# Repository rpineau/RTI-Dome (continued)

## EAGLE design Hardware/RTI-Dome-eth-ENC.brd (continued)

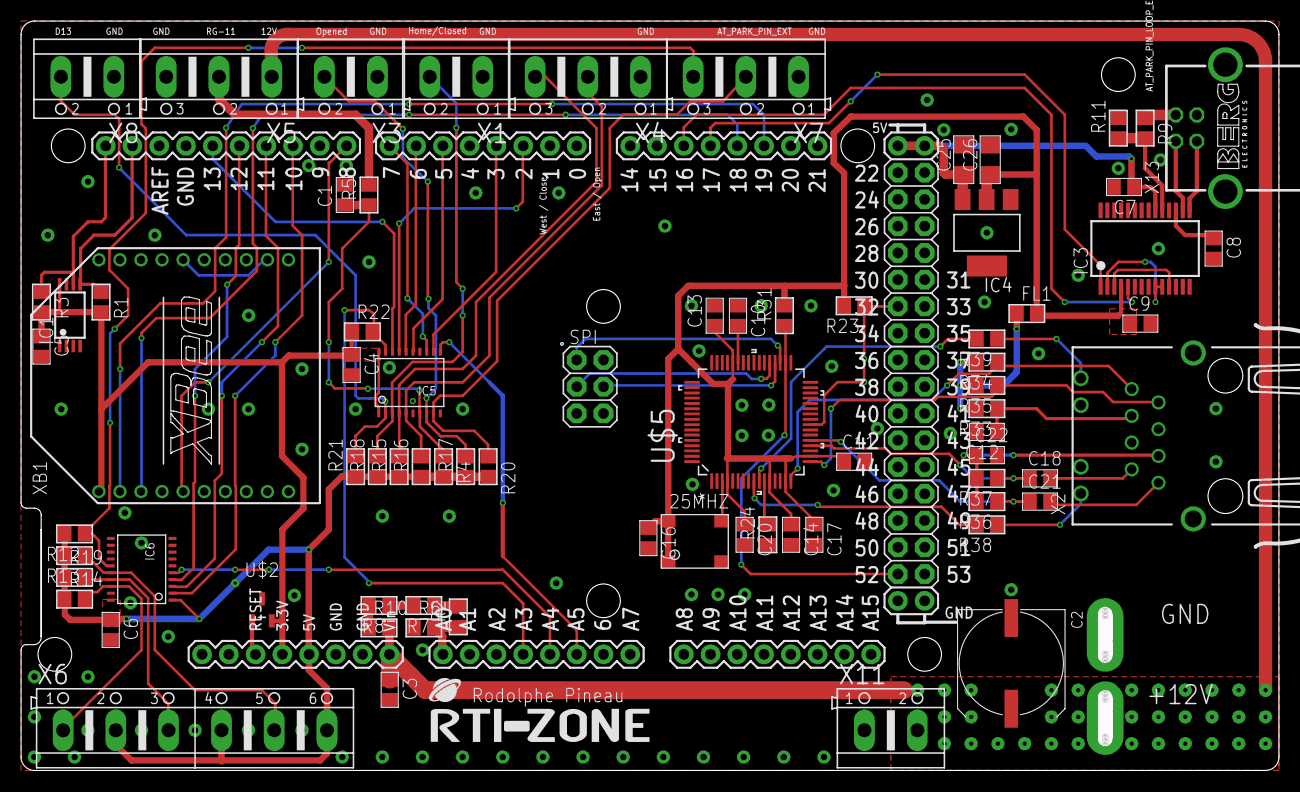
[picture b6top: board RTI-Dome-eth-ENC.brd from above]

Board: 2 copper layers, 119.4 x 71.1 mm, 77 parts (1 on the bottom side), 70 nets.

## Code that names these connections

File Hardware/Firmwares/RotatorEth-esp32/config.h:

//
// Firmware configuration
// Copyright © 2025 Rodolphe Pineau. All rights reserved.
//
#ifndef __R_CONFIG__
#define __R_CONFIG__
// #define DEBUG   // enable debug to serial port defined as DebugPort
// #define DEBUG_TO_COMPUTER // send all debug to usb serial instead of 3 pin serial debug.
// #define MOTION_LOG	// log all call to a motion function
#ifdef DEBUG
#pragma message "Debug messages enabled"
#ifndef DEBUG_TO_COMPUTER
#define DebugPort Serial1    //  Rx2,Tx2 =  Serial1
#endif
#define DBPrint(x) if(DebugPort) DebugPort.print(x)
#define DBPrintln(x) if(DebugPort) DebugPort.println(x)
#define DBPrintHex(x) if(DebugPort) DebugPort.print(x, HEX)
#else
#pragma message "Debug messages disabled"
#define DBPrint(x)
#define DBPrintln(x)
#define DBPrintHex(x)
#endif // DEBUG

#define VERSION "3.000"

#define USE_ALPACA
#define USE_OTA_UPDATE
// if uncommented, USE_WIFI will enable all code related to the shutter over WiFi.
// This is useful for people who only want to automate the rotation.
#define USE_WIFI

#define Computer Serial     // USB = Serial
#ifdef DEBUG
#ifdef DEBUG_TO_COMPUTER
#define DebugPort Serial
#endif
#endif
//
// ESP32 dev boards
//
// input
#define HOME_PIN            15  // Also used for Shutter open status
#define SPARE_OPENED_PIN 	33	// Digital Input, shutter open limit swith, not used on rotator board, spare input.
#define BUTTON_CCW          27 // Digital Input
#define BUTTON_CW           14 // Digital Input
#define CONDITION_SENSOR_PIN     25  // Digital Input from RG11 and other similar devices
#define SPARE1				34	 // no pull-up on this input pin
#define SPARE2				26
// ouput
#define STEPPER_ENABLE_PIN  13  // Digital Output
#define DIRECTION_PIN        2  // Digital Output
#define STEP_PIN            32  // Digital Output
// 100k to ground on GPIO 12, and 100k to 3.3V on GPIO 0
#define SPARE_OUT1			 0
#define SPARE_OUT2			12

#define MOVE_NEGATIVE       -1
#define MOVE_NONE            0
#define MOVE_POSITIVE        1

// #define M_ENABLE    HIGH
// #define M_DISABLE   LOW
#define M_ENABLE    LOW
#define M_DISABLE   HIGH

// A4988
//#define M_ENABLE    LOW
//#define M_DISABLE   HIGH

#define MAX_SPEED           8000
#define ACCELERATION        7000

#define DELAY_WIFI			10

/*
Micro-steps per rotation with a 200 step per rotation stepper and 15.3:1 gearbox
	NexDome 2m      : 440640
	Explora-Dome 8' : 479800
*/

#define STEPS_DEFAULT       440640

#define ETHERNET_CS     5
#define ETHERNET_INT	-1
#define ETHERNET_RESET  4
#define CMD_SERVER_PORT 2323

// network interfaces
#include <ETH.h>
#include <Network.h>
#define domeEthernet ETH

#define ETH_PHY_TYPE ETH_PHY_W5500
#define ETH_PHY_ADDR 1
#define ETH_PHY_CS   ETHERNET_CS
#define ETH_PHY_IRQ  -1
#define ETH_PHY_RST  ETHERNET_RESET

// SPI pins
#define ETH_SPI_SCK         SCK
#define ETH_SPI_MISO        MISO
#define ETH_SPI_MOSI        MOSI


#ifdef USE_WIFI
#define SHUTTER_PORT 2424
#define shutterWiFi WiFi
#endif

#ifdef USE_OTA_UPDATE
#define OTA_PORT	8080
#endif

#endif

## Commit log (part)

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2021-03-26 Code cleanup, comment/log cleanup
2021-03-26 Adding command doc
2021-03-27 Remove unused board.
2021-03-27 Adding BOM for rotator shield
2021-03-28 Making some pull-up pull-down to get a better OFF state when the controller is not powered but the stepper driver is.
2021-03-28 Pull-down doesn't really help. Setting back to pull-up to make sure enable does enable :)
2021-03-29 Remove the Reconnect code as it will not work as is and we're trying to find the issue in TSX related to TCP.
2021-03-30 Fix a non connected network on the board... the motor VOut .. :(
2021-03-30 Adding a hole to fic the board to a support.
2021-04-04 Fix a few component values.
2021-04-10 Fix a potential bug on close.
2021-04-10 Comment already defined macro for the due flash
2021-04-14 Starting to add code for drop-out shutter in the firmware
2021-05-18 Fix version in innosetup file. Added comments in firmware for number of steps per rotation for different domes.
2021-06-05 Fixing a small bug on open/close initial state. Improved the opening/closing in case of spurious interrupt.
2021-06-06 Chamge the way we check bondary after a goto. Fix some firmware stuff.
2021-06-17 Fix dome open/close issues
2021-06-17 Fix the false state for m_bWasRunning
2021-06-26 fix missing windows dll static linking for 64 bits
2021-08-21 Add proper xbee issue detection and try to not just reconfigurethe Xbee but reset it before.
2021-08-22 Code cleanup in watchdog trigger and XBee resets
2021-08-22 Fix typo
2021-08-28 Properly return an error if we try to open but it rains (the controller will not open anyway).
2021-09-02 Big code refactoring to remove all snprintf. fprintf,... and use pure C++.
2021-09-19 Add color for rain status
2021-09-19 Fix a small issue with logging code not compiling on Linux
2021-09-19 Trying to fix a bug on Linux
2021-09-19 Set debug to full
2021-10-26 Fix some logs
2022-01-28 Fix InnoSetup file to detect TSX64 install path even if TSX32 was never ran.
2022-06-05 A bit of code cleanup. Also read rain status directly in addition to the interrupt
2022-06-05 Reset interrupts every 12 hours. For some reason they stop working after a while.
2022-06-22 Fix some code for standalone mode.
2022-06-29 Update macOS notarization
2022-07-01 Fix merge conflict
2022-07-03 Small changes for rotator board without Ethernet
2022-07-29 Add a few comments in the arduino code as I'm going to start adding new features.
2022-08-30 Improved boundary check
2022-12-04 Fix some debug
2022-12-04 Set log header even at the lowest debug level
2023-02-14 Started working on a new version using the Raspberry Pi RP2040 as a future replacement for the Arduino DUE
2023-02-14 A few change in preparation of using RP2040 core0 for main tasks and core1 for stepper control
2023-02-15 Fix packages for ABT abd LVC buffers
2023-02-20 Cleaned up version for dual core RP2040
2023-03-09 Added support for the new DomeHasHighlyRelaibleOpenCloseSensors interface.
2023-03-12 Set pulse width for stepper
2023-07-09 Changing a enum to be more clear
2023-07-10 Change enable polarity
2023-08-06 Finished routing on RP2040 board
2023-08-07 moved some component to avoid colisions (3D rendring helps ! )
2023-08-11 Track cleanup on RP-2040 board
2023-08-15 Starting on V2 RP2040 board
2023-08-16 Fix some issue after the schematics snap to grid.
2023-08-18 Fix a firmware bug on 0 distance move leaving motor enabled.
2023-08-19 Fix a bug in rain parking that was keeping the motor on.
2023-08-28 Some fixes in the shutter firmware
2023-08-31 New RP2040 shutter board
2023-08-31 Switching to 0603 for resistor and capacitors
2023-09-03 small change in debug firmware for RP2040
2023-09-08 Added all the code for the RP2040
2023-10-12 Moving commmands to header files
2023-10-12 Arduino IDE breaks if there is a symlink to upper dirs ...
2023-12-26 Use std::stringstream to build commands to make it more readable.
2024-01-01 Minor changes in plugin code.
2024-03-18 Soem minor fixes on the PCB
2024-04-11 Adding Alpaca server. the few first endpoints are working.
2024-04-14 Fix some Alpaca PUT methods.
2024-04-14 Cleaned up debug for Alpaca. Disable XBee for Alapca debugging.
2024-04-16 Adding more Alpaca code
2024-04-17 More Alpaca code
2024-04-18 Added more Alpaca functions
2024-04-18 Small fix on json key access based on doc recommendation.
2024-04-18 Adding code to start decoding actions
2024-04-19 Alpaca conformance test passe for all rotator methods.
2024-04-19 Cleanup the debug
2024-04-20 Removed all Arduino DUE code. Added setup page (doesn't do anything yet).
    Also moved paramerers parsing to a function to avoid code duplication
2024-04-20 Fix a small stuff in the setup alpaca method.
2024-04-21 Added redirect to the setup page
2024-04-21 Renaming some classees.
2024-04-21 Relocate all Alpaca code from main ino file to Alpaca.h
2024-04-25 Adding initial code for shutter board using RP2040
2024-04-26 Fix shutter RP2040 pin assignements
2024-04-27 Fix Alcapa shutter fucntion to report the proper errors
2024-04-28 Some Alapca improvments
2024-04-28 Adding the same code for the RP2040 but using the lwIP_w5500 lib.
    This is still not 100% functional as the same code is 25 times
    slower to respond to queries. Next step is to wire the INT pin
    on the PCB to try to address this issue.
2024-04-28 Fixed the performance issue by wiring the W5500 interrupt tp GP27
2024-04-29 Remove copy of code as it now works
2024-04-29 Fix issue with use method on Slaved function.
2024-04-29 Code refactoring to reduce code size.
2024-04-29 More Alpaca fixes.
2024-04-30 Cleanup debug messages
2024-05-02 First pass at the firware with WiFi conntect for shutter
2024-05-04 Added a few things to the V2 board
2024-05-04 Removed XBee from RP2040 Shutter controller
2024-05-05 Fixed some issue for the TCP conenction between shuter and rotator
    This is not stable for some reason. I might try with UDP but this
    seems to be some underlaying WiFi issue as the connection drops
2024-05-06 Fix some i2c issues
2024-05-07 Adding proper timeout settings for the wifi connection
2024-05-09 Looks like the Pico WiFi is not going to work. Starting move to ESP32
2024-05-11 Adding ESP32 version of the shutter controller
2024-05-11 Set the proper version of the EXP32 kit for each board.
2024-05-17 Fix pin assignement issues for ESP32
2024-05-17 Fix a crash with ESP32 and String casting of ArduinoJson doc item
2024-05-17 More fixes for Ethernet and speed overall.
    Puting each server in a task is slowing things down (context switching)
2024-05-17 Use write instead of print as we only need to send the data.
2024-05-20 Backport some fixes from the rp2040 code to Due code.
2024-05-22 Add code to ignore get parameter case.
2024-05-28 Fix print on stream to use write instead. Much faster.
2024-06-03 Turns out the write is too fast for Xbeen config mode.
2024-06-12 Adding shutter code with ESP32
2024-09-29 Use switching regulator for the 5v. Can take from 8V to 40V in.
2024-09-29 Now using Wurth connector for rotator and shutter.
2024-10-06 Change the 5V regulator on the rotatyor esp32 board.
2024-11-13 Fix log line using __func__
2024-11-17 Re-adding the domeClient.stop();
2024-12-02 Fix some warning
2024-12-02 Fix a few compiler warning
2025-01-06 Fix Alpaca error codes.
2025-01-15 Fix WDT issue on esp32 code
2025-01-17 Fix some connection issue to ESP32. Disable TWDT on ESP32
2025-01-19 New ESP32 firmware is working.
2025-01-20 Repo cleanup
2025-02-11 Enable debug for only goto and park to test TSX issue
2025-02-11 And another typo
2025-03-08 Changing 5V circuit
2025-03-08 Better 12V input filtering
2025-05-03 Change reference to rain with safe/unsafe
2025-05-04 Remove ref to Arduino DUE
2025-06-22 Fix some alpaca issue. Now passes Conformance test (again :) ).
2025-06-29 Send rain status all the time.
2025-06-29 Cleanup useless delay() calls.
2025-07-11 I don't use extEEPROM.h
2025-07-12 same wdt works on esp23 and esp32-s3
2025-10-21 Adding all endpoints for controllers configuration
2025-10-22 Fix safe/unsafe states
2025-11-01 Remove extra eeprom save
2025-11-01 Set dome interface version to 3
2025-11-01 WiFi reconfigure works
2025-11-01 Adding command to get SSID from shutter cache
2025-11-03 Fix SSID field max length
2025-11-03 Adding some Interface V3 code
2025-11-09 No need for timestamp in device state as fields are not mandatory.
2025-11-09 Fix some Wifi stuff
2025-11-17 Set interface version to 3 which is the latest on Platform 7 for Domes.
2025-11-18 Replace all double to float to be able to leverage the ESP32 FPU (which doesn't support double).
2025-11-28 Fix UUID issue
2025-11-28 Re-export board from Fusion
2025-12-04 Fix unused param in getMacAddress
2025-12-04 Set http update port as a define
2025-12-11 Converterd all setting to using ESP32 NVS / Preferences
2025-12-24 Fix preferences.
2025-12-26 Fix calculation error on ADC for input volage
2025-12-26 Fix WiFi connection. Remove voltage reading from rotator as we don't have this on the board
2025-12-31 Fix a lot of issues with interrupt
2025-12-31 Need more button fixes.
2025-12-31 Fix a small issue with SSID change timing
2026-01-01 Fixed some bug. Debug message are on, will cleanup later
2026-01-01 Remove atomic. not reliable on ESP32/
2026-01-01 More atomic removal
2026-01-02 Significant improvment on wifi reconnect and rotator to shutter coms.
    Also fix more bugs related to the change to FastAccelStepper.
2026-01-16 Fix some interrupt debiunce in old firmware. Make llong move longer :)
2026-01-21 Fix debounce variables
2026-01-25 Chaning XBee channel to avoind issues with wifi
2026-01-25 separate east/west button processing
2026-01-25 Clear random \
2026-02-01 No need for software debouncing as the board have hardware debouncing
2026-02-02 Fix some shutter issue on old and new boards firmware
2026-02-08 Make sure the seek mode is correct when using buttons.
2026-02-12 Added code to enable open/close button on the rotator controller
2026-02-14 Preparing to update to the new ESP32 ETH.h
    This requires some changes the all the TCP server code and TCP Client.
2026-03-06 Starting to add code to manage drop off shutter
2026-04-19 Switch to ESP32 Network for all servers
2026-04-19 Fix some method name.
2026-04-25 More yaml stuff.
    cleaning up as much as I can before adding all the other endpoint.
2026-04-25 use the key "value" for all setup api call to simplify code.
2026-04-25 Improve 200 response by providing the value we just set unt a PUT
2026-04-25 Adding definition for park position
2026-05-02 Most of the configuration REST interface is done.
2026-05-02 Addming more API definition to yaml file
2026-05-02 Added all the API endpoint to the yaml file. Some are not yet inplemented in the firmware
2026-05-02 Adding web interface.
2026-05-03 Fix some UI yaml issue
2026-05-03 With RTI-Zone logo on the web ui
2026-05-03 Disable debug
2026-05-03 Change default IP in case of no DHCP.
2026-05-03 Also set the timeout on cable detection to 30 seconds
2026-05-03 Set openapi version to 3.2.0 (even if we don't use any specific 3.2.0 feature)
2026-05-03 Adding option to restore network config to defaults
2026-05-03 Fix some command comments
2026-05-05 Added control on the web UI
2026-05-05 Fix arrow rotation in UI
2026-05-05 Time to update the version to 3.0
2026-05-05 We are now only making the X2 plugin for version 3.0 and up
2026-05-06 Fix a few things in the yaml file.
2026-05-07 Fix wrong put for getShutterState, it should be a get
2026-05-07 Pull shutter state before returning vlaue
2026-05-07 Fix to the shutter web UI
2026-05-07 Adding some sync to curent position for FasStepper.
2026-05-07 Better way to deal with azimuth looping at 360
2026-05-08 Fix shutter state issue
2026-05-08 Fixing shutter status on open/close start
2026-05-08 More code cleanup in dome REST API
2026-05-09 Adding calibrate REST call.
2026-05-10 Fix command comment
2026-05-10 Added a command to reset the controllers to factory settings
2026-05-12 Added the reset to factory default.
2026-05-12 Bad comment... do it in the right place
2026-05-12 Fix settings dialog to use the SSID instead of panID.
2026-05-12 SSID as 0 to 23 char... but let's at least have 1 ..
2026-05-16 Cleanup some code
2026-05-16 Enhence the debug mode
2026-05-16 dosable activity log in UI
2026-05-16 Set defaiult dns to 1.1.1.1
2026-05-18 Adding command to enable double shutter
2026-05-19 started adding code in the X2 plugin for dual shutter control.
2026-05-25 Adding abort and fix goto value to be 0-360 when doing goto from web interfac.
2026-05-25 Revove some unneeded prefereces close.
2026-06-03 Fix some function name to be clearer.
2026-06-12 Fix pin assignement for lower shutter
2026-06-14 New web interface with fix for calibration states
2026-06-14 Fix the display when doing a put on calibration start
2026-06-14 Some shutter code cleanup.
